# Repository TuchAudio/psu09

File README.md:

# psu09
_Symmetrical_, unregulated Power Supply board for [TuchAudio 209](../../../ta209) Power Amp

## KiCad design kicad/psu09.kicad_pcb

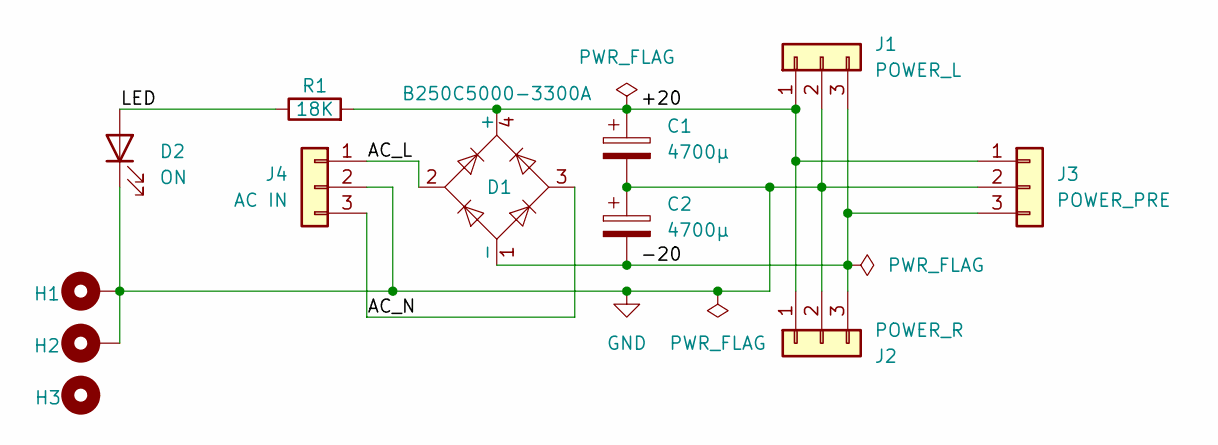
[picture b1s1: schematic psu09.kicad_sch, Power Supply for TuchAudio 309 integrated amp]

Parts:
C1, C2: 4700µ; CP_Axial_L42.0mm_D29.0mm_P45.00mm_Horizontal
D1: B250C5000-3300A; Diode_Bridge_32.0x5.6x17.0mm_P10.0mm_P7.5mm
D2: ON; PinHeader_1x02_P2.54mm_Vertical
H1, H2: MountingHole_Pad; MountingHole_3.2mm_M3_DIN965_Pad
H3: MountingHole; MountingHole_3.2mm_M3_DIN965
J1: POWER_L; TerminalBlock_MaiXu_MX126-5.0-03P_1x03_P5.00mm
J2: POWER_R; TerminalBlock_MaiXu_MX126-5.0-03P_1x03_P5.00mm
J3: POWER_PRE; PinHeader_1x03_P2.54mm_Vertical
J4: AC IN; TerminalBlock_MaiXu_MX126-5.0-03P_1x03_P5.00mm
R1: 18K; R_Axial_DIN0207_L6.3mm_D2.5mm_P10.16mm_Horizontal

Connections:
/+20: C1.1, D1.4 (+), J1.1, J2.1, J3.1, R1.2
/-20: C2.2, D1.1 (-), J1.3, J2.3, J3.3
/AC_L: D1.2, J4.1
/AC_N: D1.3, J4.3
/LED: D2.2 (A), R1.1
GND: C1.2, C2.1, D2.1 (K), H1.1, H2.1, J1.2, J2.2, J3.2, J4.2

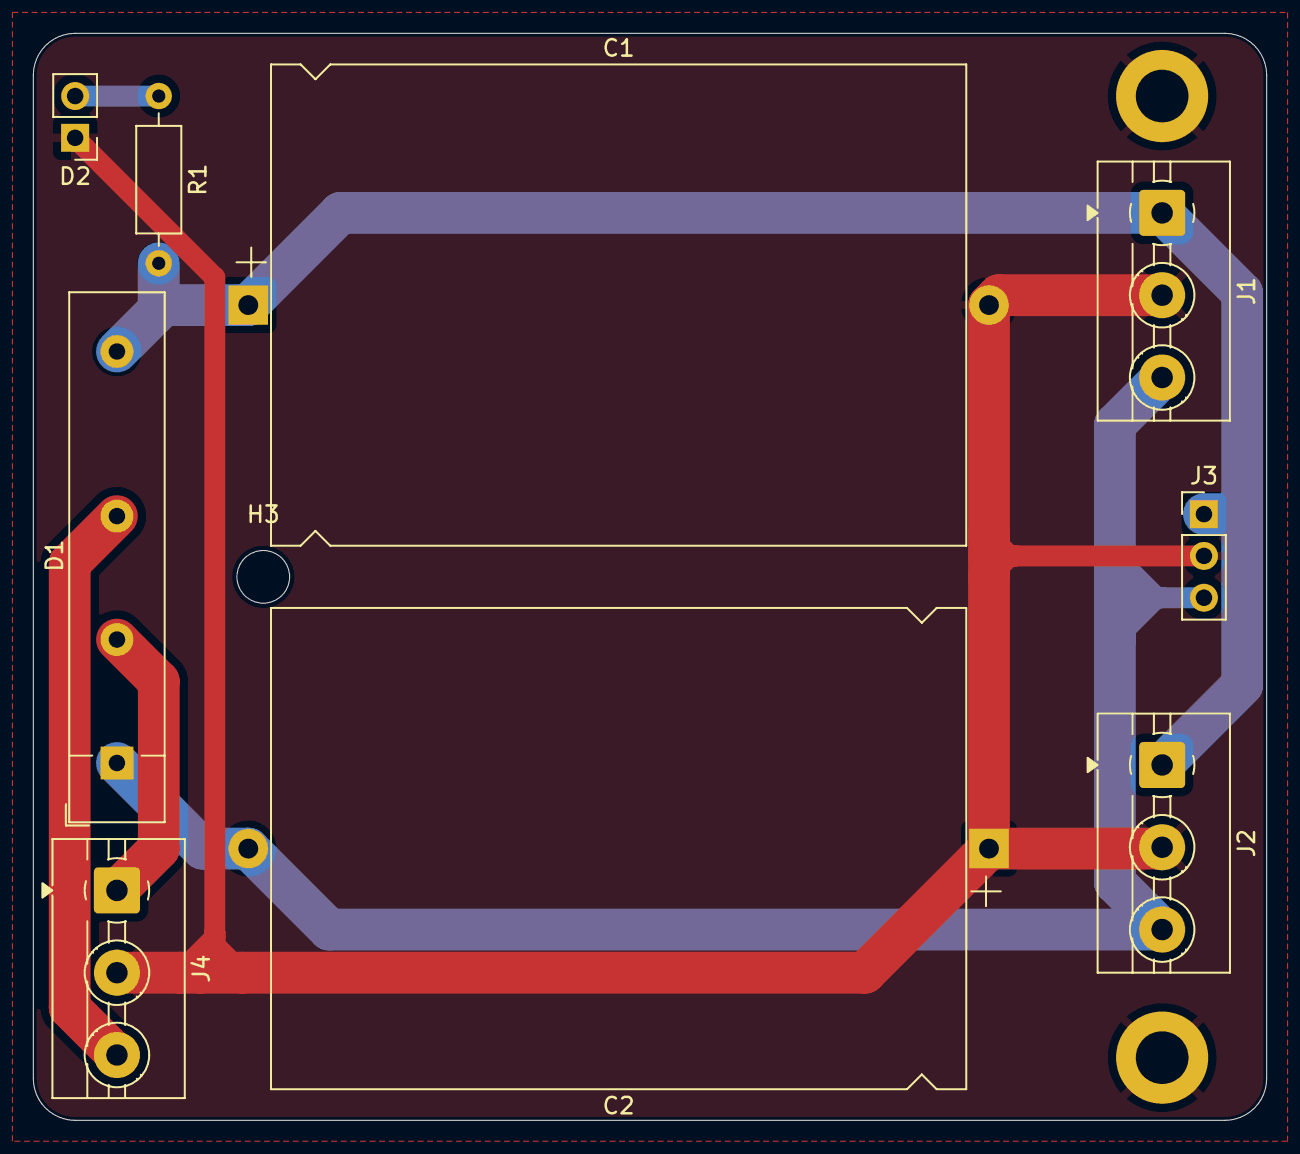
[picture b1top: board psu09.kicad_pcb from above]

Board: 2 copper layers, 74.9 x 66.0 mm, 12 parts (0 on the bottom side), 6 nets.

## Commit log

2025-11-08 add KiCAD files
2025-11-24 link and basic specs
